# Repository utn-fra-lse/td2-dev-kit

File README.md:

# td2-dev-kit

El objetivo de este kit de desarrollo es proveer un hardware común para las plataformas de la cátedra de Técnicas Digitales II, siendo estas el ESP32 y la Raspberry Pi Pico 2.

## Pinouts de placas de desarrollo

Abajo están los pinouts de las placas de desarrollo que usamos en la cátedra

### ESP32 Devkit C1

### Raspberry Pi Pico 2W

## Kit de desarrollo

Este va a ser nuestro kit de desarrollo para toda la cátedra.

Tiene una variedad de periféricos para poder usar que a continuación vamos a mencionar brevemente.

### Entradas y salidas digitales

| GPIO RPico 2W | GPIO ESP32 | Dispositivo |
| --- | --- | --- |
| 2 | 9 | Output A de encoder rotativo |
| 3 | 10 | Output B de encoder rotativo |
| 12 | 37 | Botón de encoder rotativo |
| 11 | 8 | Buzzer pasivo |
| 10 | 38 | Ánodo LED individual |
| 15 | 5 | Cátodo LED rojo (RGB) |
| 13 | 6 | Cátodo LED verde (RGB) |
| 14 | 7 | Cátodo LED azul (RGB) | 

### Entradas analógicas

| GPIO RPico 2W | GPIO ESP32 | Dispositivo |
| --- | --- | --- |
| 26 | 1 | Micrófono |
| 27 | 2 | Potenciómetro |
| 28 | 4 | Termistor NTC |

En los tres casos, es posible anular las tres entradas analógicas a través de los jumpers `JP1`, `JP2` y `JP3` respectivamente. Al hacerlo, se puede conectar alguna entrada analógica externa con los conectores `J5`, `J6` y `J7`.

### Salida analógica

El kit provee una salida analógica a partir de PWM o DAC puro. Es posible medir la salida en `J8` o conectarla a un osciloscopio con el BNC provisto en `J11`.

| Microcontrolador | GPIO |
| --- | --- |
| RPico 2W | 22 |
| ESP32 | 21 |

En ambos casos, el GPIO disponible solo puede generar PWM pero se provee un seguidor de tensión con un filtro pasa bajos para convertir la salida de PWM en una salida analógica pura.

### Sensores y pantallas (I2C)

Todos los sensores y pantallas funcionan en el mismo bus de I2C como esclavos. Entre ellos tenemos:

* BME280 (Sensor de presión, humedad y temperatura).
* BH1750 (Sensor de luminosidad).
* MPU6050 (Acelerómetro y giróscopo).
* SSD1306 (Pantalla monocromática OLED de 128x32).

| Microcontrolador | I2C SDA | I2C SCL |
| --- | --- | --- |
| RPico 2W | 4 | 5 |
| ESP32 | 35 | 36 |

> En el caso del ESP32, es factible elegir cualquier bus. En la Raspberry Pi Pico 2W es el bus de I2C0.

Se provee un conector `J2` con los cuatro pines necesarios para conectar algún otro dispositivo I2C si fuese necesario.

### Tarjeta microSD

El kit provee las conexiones para hacer uso de almacenamiento en una microSD directamente por SPI.

| Microcontrolador | SPI MOSI | SPI MISO | SPI SCK | SPI CS |
| --- | --- | --- | --- | --- |
| RPico 2W | 19 | 16 | 18 | 17 |
| ESP32 | 48 | 45 | 47 | 46 |

> El bus de SPI para la Raspberry Pi Pico es el SPI0 mientras qye en el ESP32 es posible elegirlo.

Es posible anular la SD removiendo `JP4` y usando el conector `J3` para acceder a otro dispositivo SPI externo usando las mismas conexiones.

### UART

Si bien no se provee ningún dispositivo por UART en el propio kit, se deja la conexión disponible para usar a gusto con cualquier dispositivo externo.

| Microcontrolador | UART TX | UART RX |
| --- | --- | --- |
| RPico 2W | 8 | 9 |
| ESP32 | 43 | 44 |

> En la Raspberry Pi Pico 2W el UART usado es el UART1 mientras que en el ESP32 es el UART0.

### Debug Probe

En el caso del ESP32, este viene con un debugger en el propio kit. La Raspberry Pi Pico 2W no posee un debugger propio, por lo que se provee uno embebido en el kit de la cátedra en la forma de un RP2040. Este microcontrolador puede usarse para debuggear la Raspberry Pi Pico 2W o podría usarse como un microcontrolador adicional que agrega otros 14 GPIO disponibles en `J9` y `J10`.

### Test points

Se recopilaron las señales más relevantes en test points a lo largo de todo el kit.

| Test Point | Señal |
| --- | --- |
| TP1 | Salida del micrófono previo a amplificarse |
| TP2 | Canal analógico 0 |
| TP3 | Canal analógico 1 |
| TP4 | Canal analógico 2 |
| TP5 | PWM previo al filtro pasa bajos |
| TP6 | DAC puro |
| TP7 | RGB LED rojo |
| TP8 | RGB LED verde |
| TP9 | RGB LED azul |
| TP10 | LED amarillo |
| TP11 | Salida A del encoder |
| TP12 | Salida B del encoder |
| TP13 | Pulsador del encoder |
| TP14 | UART Tx |
| TP15 | UART Rx |
| TP16 | I2C SDA |
| TP17 | I2C SCL |
| TP18 | SPI MOSI |
| TP19 | SPI MISO |
| TP20 | SPI SCK |
| TP21 | SPI CS |
| TP22 | 3.3V |
| TP23 | 5V |
| TP24 | GND |
| TP25 | RESET |

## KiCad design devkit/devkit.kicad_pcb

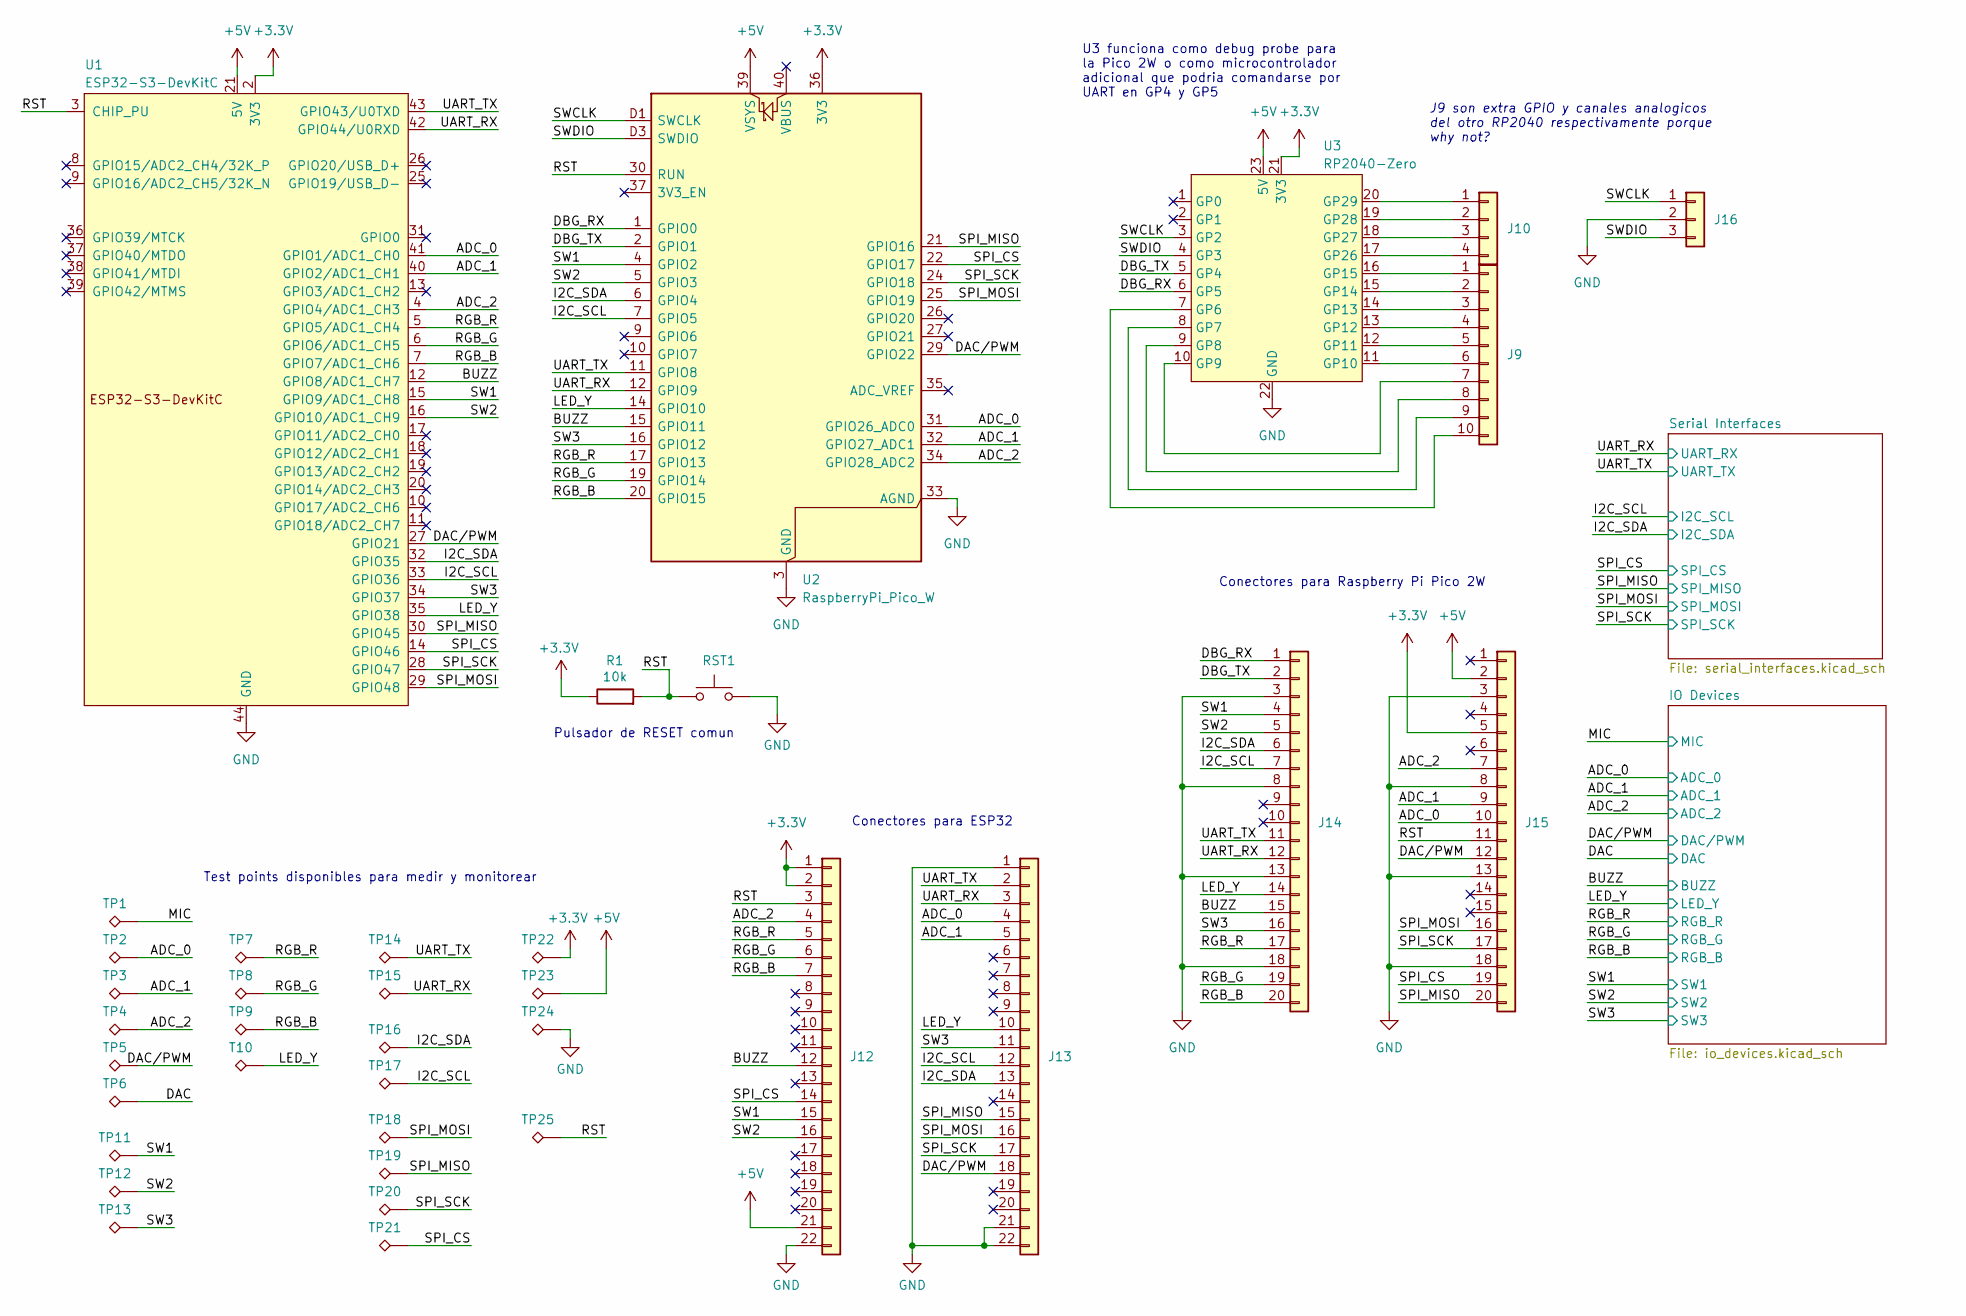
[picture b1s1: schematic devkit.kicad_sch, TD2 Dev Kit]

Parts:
J9: Conn_01x10; PinHeader_1x10_P2.54mm_Vertical
J10: Conn_01x04; PinHeader_1x04_P2.54mm_Vertical
J12, J13: Conn_01x22; PinSocket_1x22_P2.54mm_Vertical
J14, J15: Conn_01x20; PinSocket_1x20_P2.54mm_Vertical
J16: Conn_01x03; PinSocket_1x03_P2.54mm_Vertical
R1: 10k; R_0805_2012Metric_Pad1.20x1.40mm_HandSolder
RST1: RST; SW_Push_1P1T_NO_Vertical_Wuerth_434133025816
T10: TestPoint_Alt; PinHeader_1x01_P2.54mm_Vertical
TP1, TP2, TP3, TP4, TP5, TP6, TP7, TP8, TP9, TP11, TP12, TP13, TP14, TP15, TP16, TP17, TP18, TP19, TP20, TP21, TP22, TP23, TP24, TP25: TestPoint_Alt; PinHeader_1x01_P2.54mm_Vertical
U1: ESP32-S3-DevKitC
U2: RaspberryPi_Pico_W; RaspberryPi_Pico_Common_THT
U3: RP2040-Zero

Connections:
+3.3V: J12.1, J12.2, J15.5, R1.1, TP22.1, U1.1 (3V3), U1.2 (3V3), U2.36 (3V3), U3.21 (3V3); also elsewhere on the board
+5V: J12.21, J15.2, TP23.1, U1.21 (5V), U2.39 (VSYS), U3.23 (5V); also elsewhere on the board
/ADC_0: J13.4, J15.10, TP2.1, U1.41 (GPIO1/ADC1_CH0), U2.31 (GPIO26_ADC0); also elsewhere on the board
/ADC_1: J13.5, J15.9, TP3.1, U1.40 (GPIO2/ADC1_CH1), U2.32 (GPIO27_ADC1); also elsewhere on the board
/ADC_2: J12.4, J15.7, TP4.1, U1.4 (GPIO4/ADC1_CH3), U2.34 (GPIO28_ADC2); also elsewhere on the board
/BUZZ: J12.12, J14.15, U1.12 (GPIO8/ADC1_CH7), U2.15 (GPIO11); also elsewhere on the board
/DAC: TP6.1; also elsewhere on the board
/DAC/PWM: J13.18, J15.12, TP5.1, U1.27 (GPIO21), U2.29 (GPIO22); also elsewhere on the board
/DBG_RX: J14.1, U2.1 (GPIO0), U3.6 (GP5)
/DBG_TX: J14.2, U2.2 (GPIO1), U3.5 (GP4)
/I2C_SCL: J13.12, J14.7, TP17.1, U1.33 (GPIO36), U2.7 (GPIO5); also elsewhere on the board
/I2C_SDA: J13.13, J14.6, TP16.1, U1.32 (GPIO35), U2.6 (GPIO4); also elsewhere on the board
/LED_Y: J13.10, J14.14, T10.1, U1.35 (GPIO38), U2.14 (GPIO10); also elsewhere on the board
/MIC: TP1.1; also elsewhere on the board
/RGB_B: J12.7, J14.20, TP9.1, U1.7 (GPIO7/ADC1_CH6), U2.20 (GPIO15); also elsewhere on the board
/RGB_G: J12.6, J14.19, TP8.1, U1.6 (GPIO6/ADC1_CH5), U2.19 (GPIO14); also elsewhere on the board
/RGB_R: J12.5, J14.17, TP7.1, U1.5 (GPIO5/ADC1_CH4), U2.17 (GPIO13); also elsewhere on the board
/RST: J12.3, J15.11, R1.2, RST1.2, TP25.1, U1.3 (CHIP_PU), U2.30 (RUN); also elsewhere on the board
/SPI_CS: J12.14, J15.19, TP21.1, U1.14 (GPIO46), U2.22 (GPIO17); also elsewhere on the board
/SPI_MISO: J13.15, J15.20, TP19.1, U1.30 (GPIO45), U2.21 (GPIO16); also elsewhere on the board
/SPI_MOSI: J13.16, J15.16, TP18.1, U1.29 (GPIO48), U2.25 (GPIO19); also elsewhere on the board
/SPI_SCK: J13.17, J15.17, TP20.1, U1.28 (GPIO47), U2.24 (GPIO18); also elsewhere on the board
/SW1: J12.15, J14.4, TP11.1, U1.15 (GPIO9/ADC1_CH8), U2.4 (GPIO2); also elsewhere on the board
/SW2: J12.16, J14.5, TP12.1, U1.16 (GPIO10/ADC1_CH9), U2.5 (GPIO3); also elsewhere on the board
/SW3: J13.11, J14.16, TP13.1, U1.34 (GPIO37), U2.16 (GPIO12); also elsewhere on the board
/SWCLK: J16.1, U2.D1 (SWCLK), U3.3 (GP2)
/SWDIO: J16.3, U2.D3 (SWDIO), U3.4 (GP3)
/UART_RX: J13.3, J14.12, TP15.1, U1.42 (GPIO44/U0RXD), U2.12 (GPIO9); also elsewhere on the board
/UART_TX: J13.2, J14.11, TP14.1, U1.43 (GPIO43/U0TXD), U2.11 (GPIO8); also elsewhere on the board
GND: J12.22, J13.1, J13.21, J13.22, J14.3, J14.8, J14.13, J14.18, J15.3, J15.8, J15.13, J15.18, J16.2, RST1.1, TP24.1, U1.22 (GND), U1.23 (GND), U1.24 (GND), U1.44 (GND), U2.3 (GND), U2.8 (GND), U2.13 (GND), U2.18 (GND), U2.23 (GND), U2.28 (GND), U2.33 (AGND), U2.38 (GND), U2.D2 (GND), U3.22 (GND); also elsewhere on the board
unnamed: J9.1, U3.16 (GP15)
unnamed: J9.2, U3.15 (GP14)
unnamed: J9.3, U3.14 (GP13)
unnamed: J9.4, U3.13 (GP12)
unnamed: J9.5, U3.12 (GP11)
unnamed: J9.6, U3.11 (GP10)
unnamed: J9.7, U3.10 (GP9)
unnamed: J9.8, U3.9 (GP8)
unnamed: J9.9, U3.8 (GP7)
unnamed: J9.10, U3.7 (GP6)
unnamed: J10.1, U3.20 (GP29)
unnamed: J10.2, U3.19 (GP28)
unnamed: J10.3, U3.18 (GP27)
unnamed: J10.4, U3.17 (GP26)

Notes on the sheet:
J9 son extra GPIO y canales analogicos del otro RP2040 respectivamente porque why not?
Conectores para ESP32
Test points disponibles para medir y monitorear
Conectores para Raspberry Pi Pico 2W
U3 funciona como debug probe para la Pico 2W o como microcontrolador adicional que podria comandarse por UART en GP4 y GP5
Pulsador de RESET comun

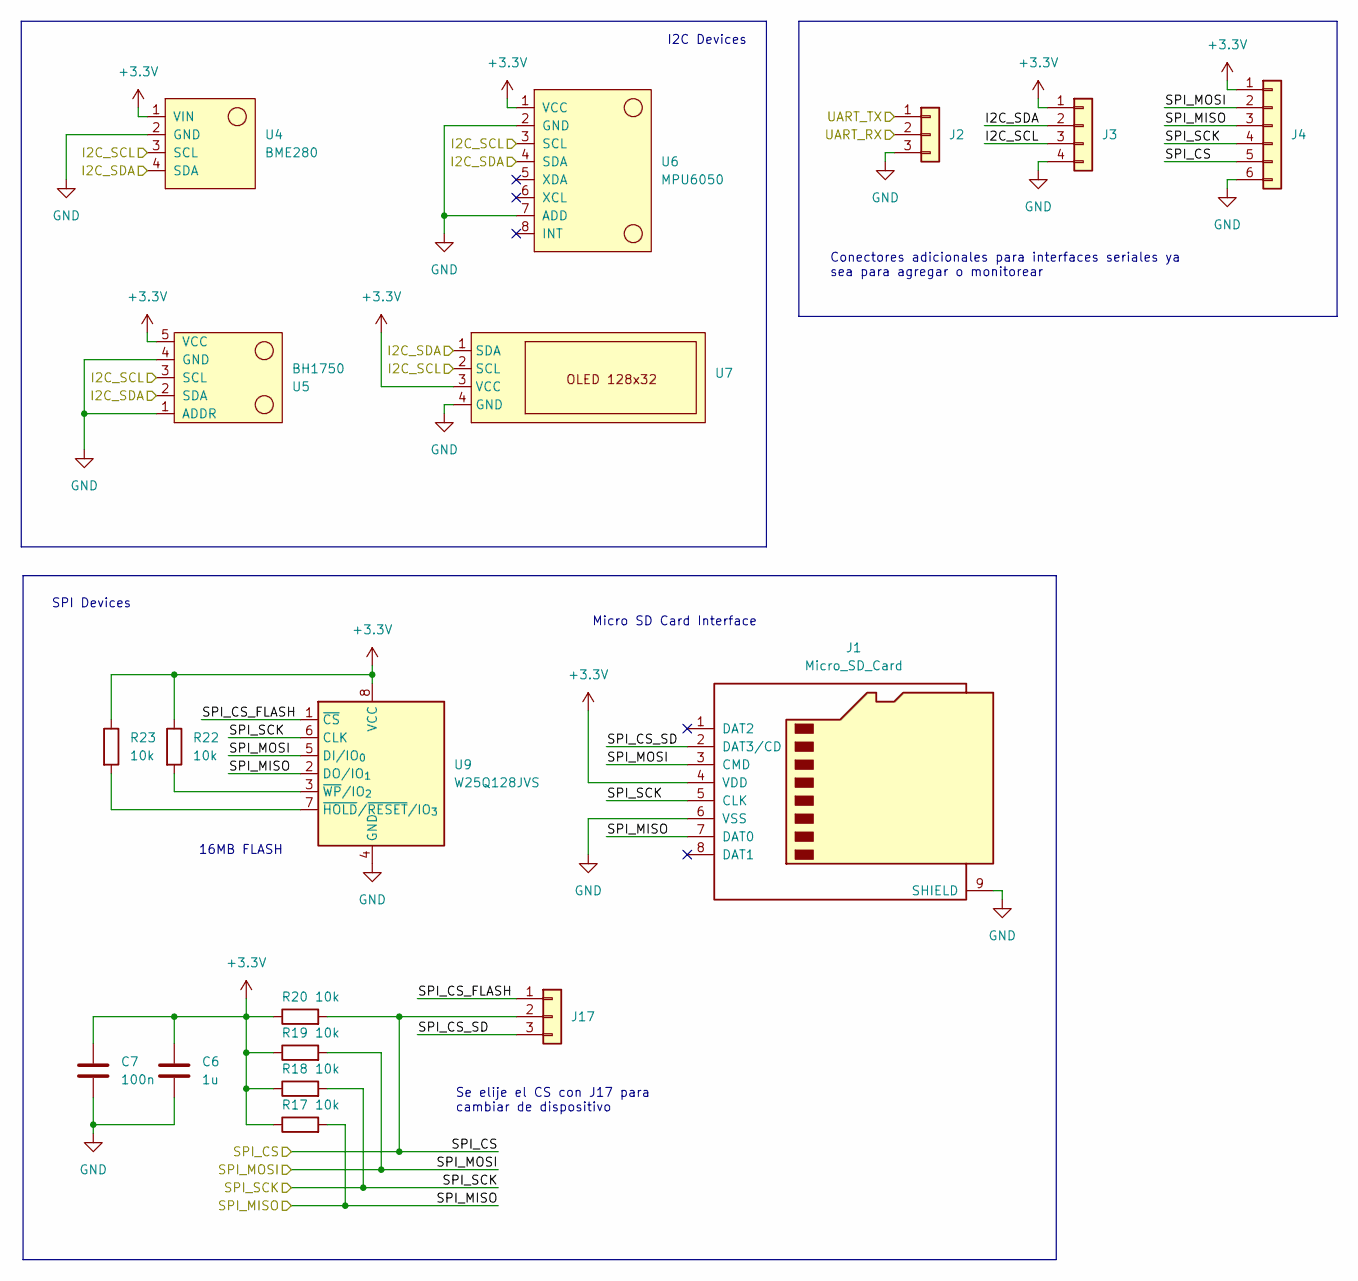
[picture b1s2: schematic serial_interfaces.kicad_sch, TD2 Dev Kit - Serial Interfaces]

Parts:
C6: 1u; C_0805_2012Metric_Pad1.18x1.45mm_HandSolder
C7: 100n; C_0805_2012Metric_Pad1.18x1.45mm_HandSolder
J1: Micro_SD_Card; microSD_HC_Molex_104031-0811
J2: Conn_01x03; PinHeader_1x03_P2.54mm_Horizontal
J3: Conn_01x04; PinHeader_1x04_P2.54mm_Horizontal
J4: Conn_01x06; PinHeader_1x06_P2.54mm_Horizontal
J17: Conn_01x03; PinHeader_1x03_P2.54mm_Vertical
R17, R18, R19, R20, R22, R23: 10k; R_0805_2012Metric_Pad1.20x1.40mm_HandSolder
U4: BME280; module_bme280_alt
U5: BH1750; module_bh1750
U6: MPU6050; module_mpu6050
U7: 128x32-OLED
U9: W25Q128JVS; SOIC-8_5.3x5.3mm_P1.27mm

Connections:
+3.3V: C6.1, C7.1, J1.4 (VDD), J3.1, J4.1, R17.1, R18.1, R19.1, R20.1, R22.1, R23.1, U4.1 (VIN), U5.5 (VCC), U6.1 (VCC), U7.3 (VCC), U9.8 (VCC); also elsewhere on the board
/I2C_SCL: J3.3, U4.3 (SCL), U5.3 (SCL), U6.3 (SCL), U7.2 (SCL); also elsewhere on the board
/I2C_SDA: J3.2, U4.4 (SDA), U5.2 (SDA), U6.4 (SDA), U7.1 (SDA); also elsewhere on the board
/SPI_CS: J4.5, J17.2, R20.2; also elsewhere on the board
/SPI_MISO: J1.7 (DAT0), J4.3, R17.2, U9.2 (DO/IO_{1}); also elsewhere on the board
/SPI_MOSI: J1.3 (CMD), J4.2, R19.2, U9.5 (DI/IO_{0}); also elsewhere on the board
/SPI_SCK: J1.5 (CLK), J4.4, R18.2, U9.6 (CLK); also elsewhere on the board
/Serial Interfaces/SPI_CS_FLASH: J17.1, U9.1 (~CS)
/Serial Interfaces/SPI_CS_SD: J1.2 (DAT3/CD), J17.3
/UART_RX: J2.2; also elsewhere on the board
/UART_TX: J2.1; also elsewhere on the board
GND: C6.2, C7.2, J1.6 (VSS), J1.9 (SHIELD), J1.10, J1.11, J2.3, J3.4, J4.6, U4.2 (GND), U5.1 (ADDR), U5.4 (GND), U6.2 (GND), U6.7 (ADD), U7.4 (GND), U9.4 (GND); also elsewhere on the board
unnamed: R23.2, U9.7 (~HOLD/~RESET/IO_{3})
unnamed: R22.2, U9.3 (~WP/IO_{2})

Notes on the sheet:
Conectores adicionales para interfaces seriales ya sea para agregar o monitorear
Se elije el CS con J17 para cambiar de dispositivo
I2C Devices
Micro SD Card Interface
16MB FLASH
SPI Devices

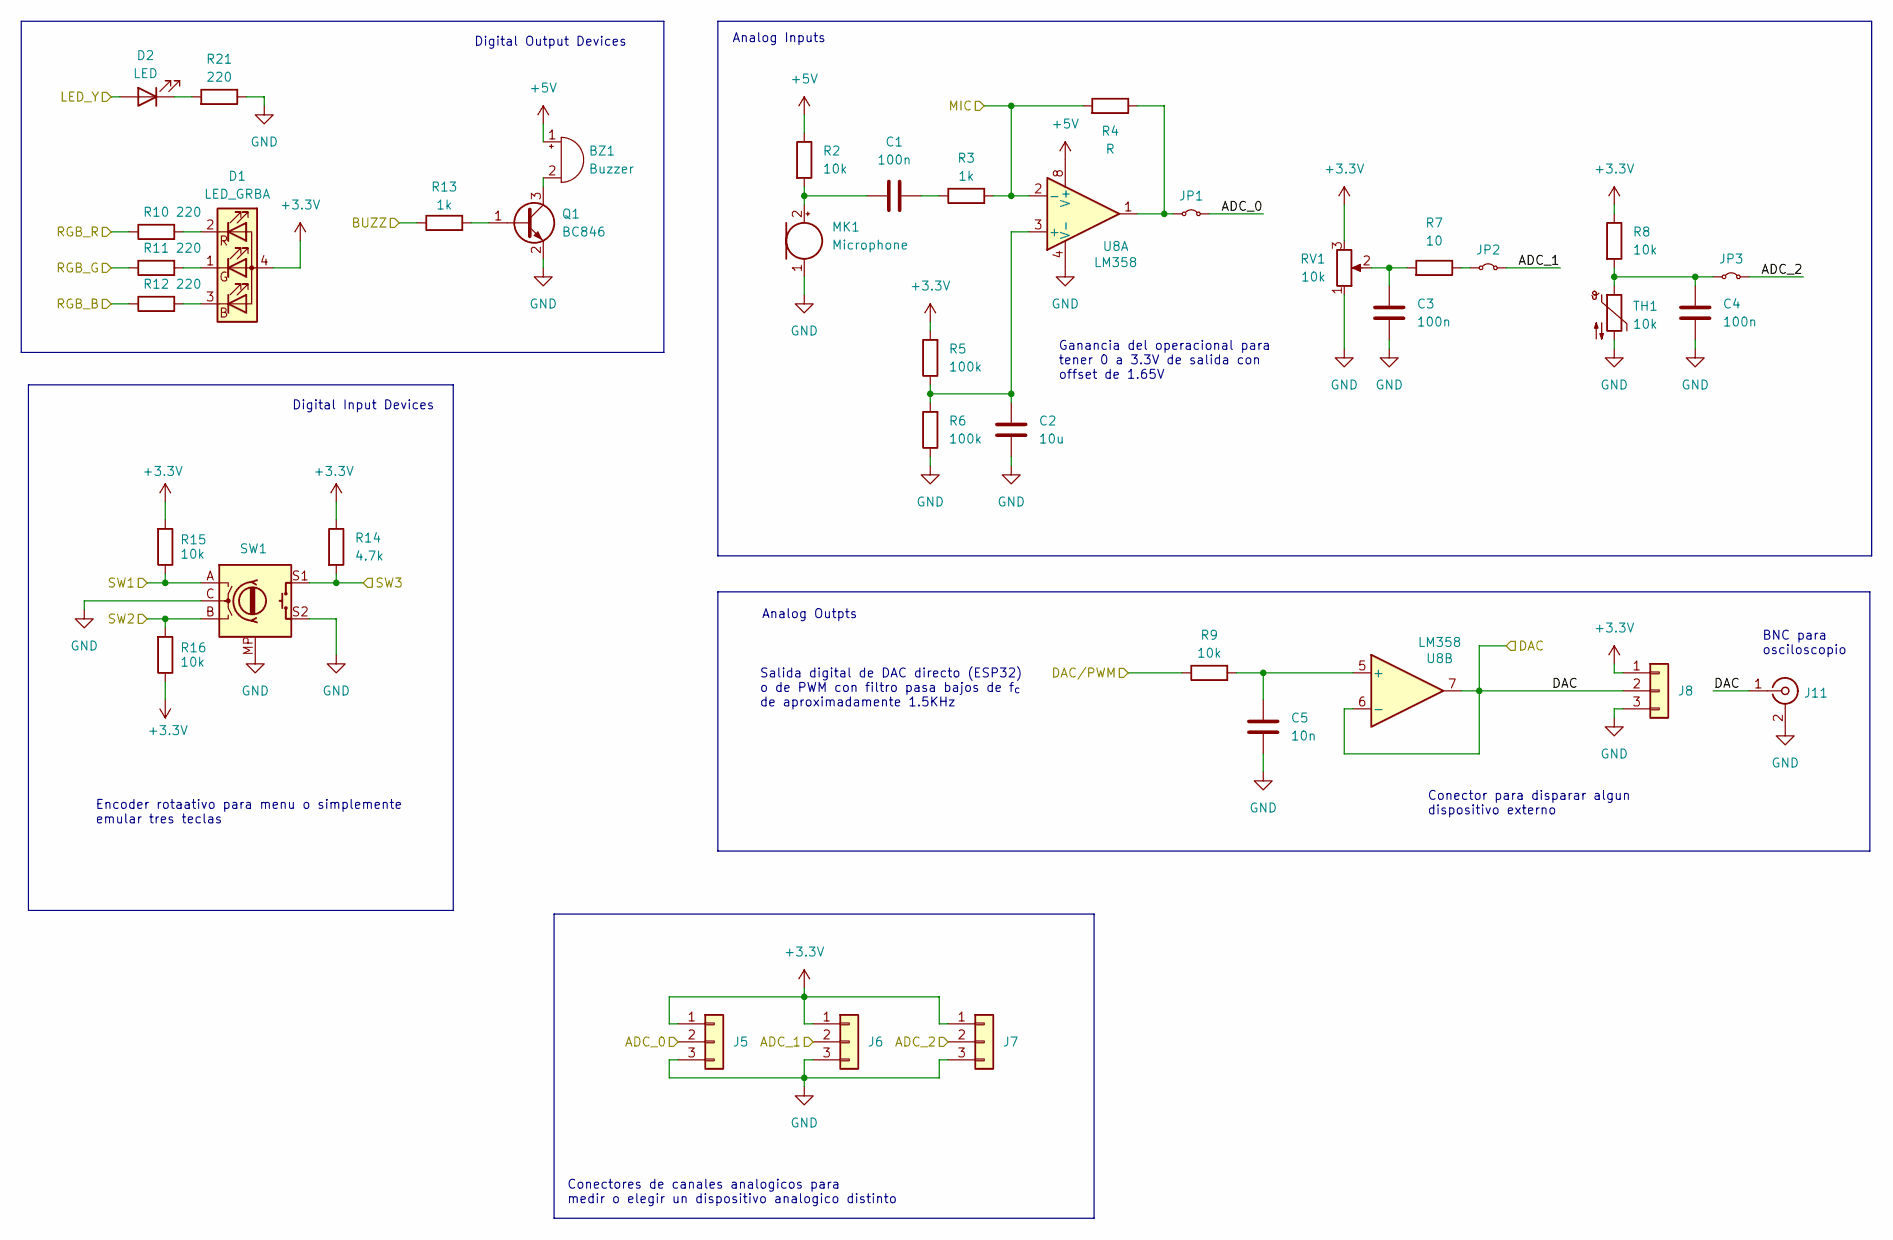
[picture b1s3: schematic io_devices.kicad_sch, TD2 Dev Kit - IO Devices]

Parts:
BZ1: Buzzer; Buzzer_12x9.5RM7.6
C1, C3, C4: 100n; C_0805_2012Metric_Pad1.18x1.45mm_HandSolder
C2: 10u; C_0805_2012Metric_Pad1.18x1.45mm_HandSolder
C5: 10n; C_0805_2012Metric_Pad1.18x1.45mm_HandSolder
D1: LED_GRBA; LED_Avago_PLCC4_3.2x2.8mm_CW
D2: LED; LED_0805_2012Metric_Pad1.15x1.40mm_HandSolder
J5, J6, J7, J8: Conn_01x03; PinHeader_1x03_P2.54mm_Horizontal
J11: Conn_Coaxial; BNC_Amphenol_B6252HB-NPP3G-50_Horizontal
JP1, JP2, JP3: Jumper_2_Small_Bridged; PinHeader_1x02_P2.54mm_Vertical
MK1: Microphone; POM-2244P-C3310-2-R
Q1: BC846; SOT-23
R2, R8, R9, R15, R16: 10k; R_0805_2012Metric_Pad1.20x1.40mm_HandSolder
R3, R13: 1k; R_0805_2012Metric_Pad1.20x1.40mm_HandSolder
R4: R; R_0805_2012Metric_Pad1.20x1.40mm_HandSolder
R5, R6: 100k; R_0805_2012Metric_Pad1.20x1.40mm_HandSolder
R7: 10; R_0805_2012Metric_Pad1.20x1.40mm_HandSolder
R10, R11, R12, R21: 220; R_0805_2012Metric_Pad1.20x1.40mm_HandSolder
R14: 4.7k; R_0805_2012Metric_Pad1.20x1.40mm_HandSolder
RV1: 10k; Potentiometer_ACP_CA9-V10_Vertical
SW1: RotaryEncoder_Switch_MP; RotaryEncoder_Alps_EC11E-Switch_Vertical_H20mm
TH1: 10k; C_Disc_D5.0mm_W2.5mm_P2.50mm
U8: LM358; SOIC-8_5.3x6.2mm_P1.27mm

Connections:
+3.3V: D1.4 (A), J5.1, J6.1, J7.1, J8.1, R5.2, R8.1, R14.1, R15.2, R16.1, RV1.3; also elsewhere on the board
+5V: BZ1.1 (+), R2.1, U8.8 (V+); also elsewhere on the board
/ADC_0: J5.2, JP1.2 (B); also elsewhere on the board
/ADC_1: J6.2, JP2.2 (B); also elsewhere on the board
/ADC_2: J7.2, JP3.2 (B); also elsewhere on the board
/BUZZ: R13.1; also elsewhere on the board
/DAC: J8.2, J11.1 (In), U8.6 (-), U8.7; also elsewhere on the board
/DAC/PWM: R9.1; also elsewhere on the board
/LED_Y: D2.2 (A); also elsewhere on the board
/MIC: R3.2, R4.2, U8.2 (-); also elsewhere on the board
/RGB_B: R12.1; also elsewhere on the board
/RGB_G: R11.1; also elsewhere on the board
/RGB_R: R10.1; also elsewhere on the board
/SW1: R15.1, SW1.A; also elsewhere on the board
/SW2: R16.2, SW1.B; also elsewhere on the board
/SW3: R14.2, SW1.S1; also elsewhere on the board
GND: C2.2, C3.2, C4.2, C5.2, J5.3, J6.3, J7.3, J8.3, J11.2 (Ext), MK1.1 (-), Q1.2 (E), R6.1, R21.1, RV1.1, SW1.C, SW1.MP, SW1.S2, TH1.2, U8.4 (V-); also elsewhere on the board
unnamed: BZ1.2 (-), Q1.3 (C)
unnamed: C1.2, R3.1
unnamed: C3.1, R7.2, RV1.2
unnamed: D1.3 (BK), R12.2
unnamed: D1.1 (GK), R11.2
unnamed: D1.2 (RK), R10.2
unnamed: D2.1 (K), R21.2
unnamed: JP1.1 (A), R4.1, U8.1
unnamed: JP2.1 (A), R7.1
unnamed: C4.1, JP3.1 (A), R8.2, TH1.1
unnamed: C1.1, MK1.2 (+), R2.2
unnamed: Q1.1 (B), R13.2
unnamed: C2.1, R5.1, R6.2, U8.3 (+)
unnamed: C5.1, R9.2, U8.5 (+)

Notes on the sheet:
BNC para osciloscopio
Analog Inputs
Digital Input Devices
Encoder rotaativo para menu o simplemente emular tres teclas
Analog Outpts
Digital Output Devices
Salida digital de DAC directo (ESP32) o de PWM con filtro pasa bajos de f_{c} de aproximadamente 1.5KHz
Ganancia del operacional para tener 0 a 3.3V de salida con offset de 1.65V
Conectores de canales analogicos para medir o elegir un dispositivo analogico distinto
Conector para disparar algun dispositivo externo

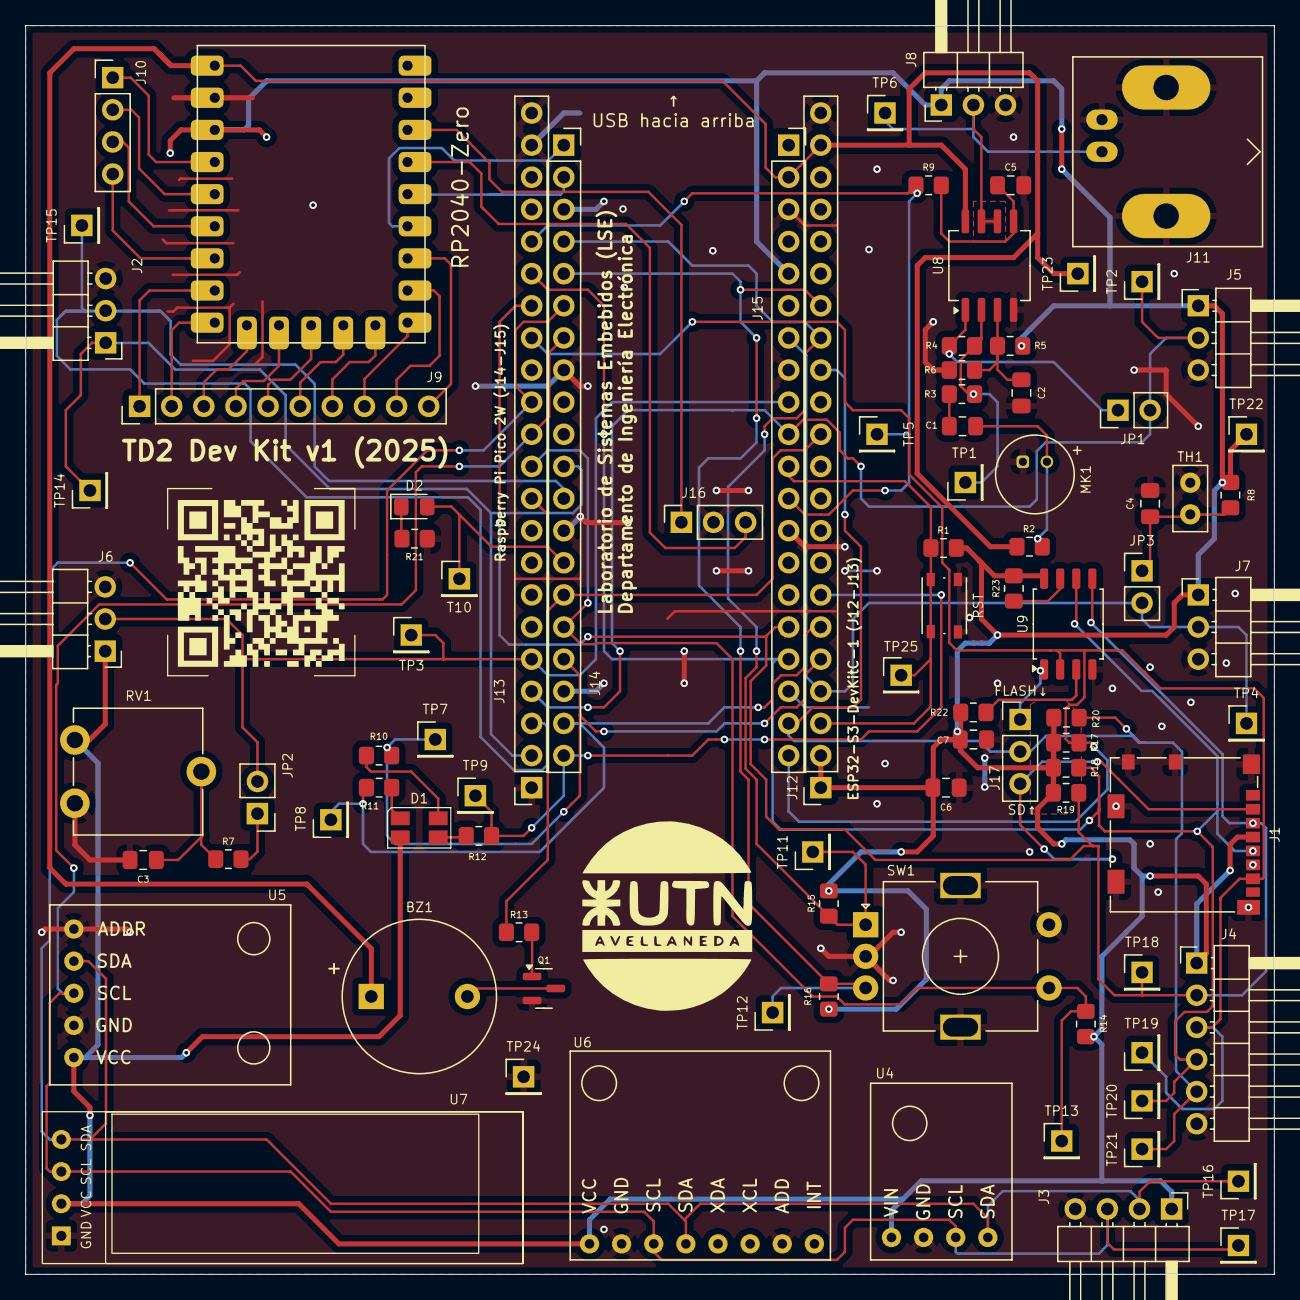
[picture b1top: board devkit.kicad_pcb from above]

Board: 2 copper layers, 98.7 x 98.7 mm, 91 parts (0 on the bottom side), 62 nets.

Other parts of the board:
RST: RST; SW_Push_1P1T_NO_Vertical_Wuerth_434133025816

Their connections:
/RST: RST.2; also elsewhere on the board
GND: RST.1; also elsewhere on the board

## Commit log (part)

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2025-07-01 feat: primer version de esquematico y pcb
2025-07-01 chore: imagenes
2025-07-01 docs: readme con descripcion basica del kit
2025-07-02 chore: actualizo vista 3d
2025-07-02 chore: logos y qr para pcb
2025-07-02 chore: cambio modelo 3d del bnc
2025-07-02 chore: actualizo algunas huellas e info en pcb
2025-07-02 chore: qr al repositorio
2025-07-16 feat: adicion de memoria flash
2025-09-03 fix: corrección re referencias de pines de LEDs de la Raspberry Pi Pico
2026-05-22 fix: fix sd connector orientation
